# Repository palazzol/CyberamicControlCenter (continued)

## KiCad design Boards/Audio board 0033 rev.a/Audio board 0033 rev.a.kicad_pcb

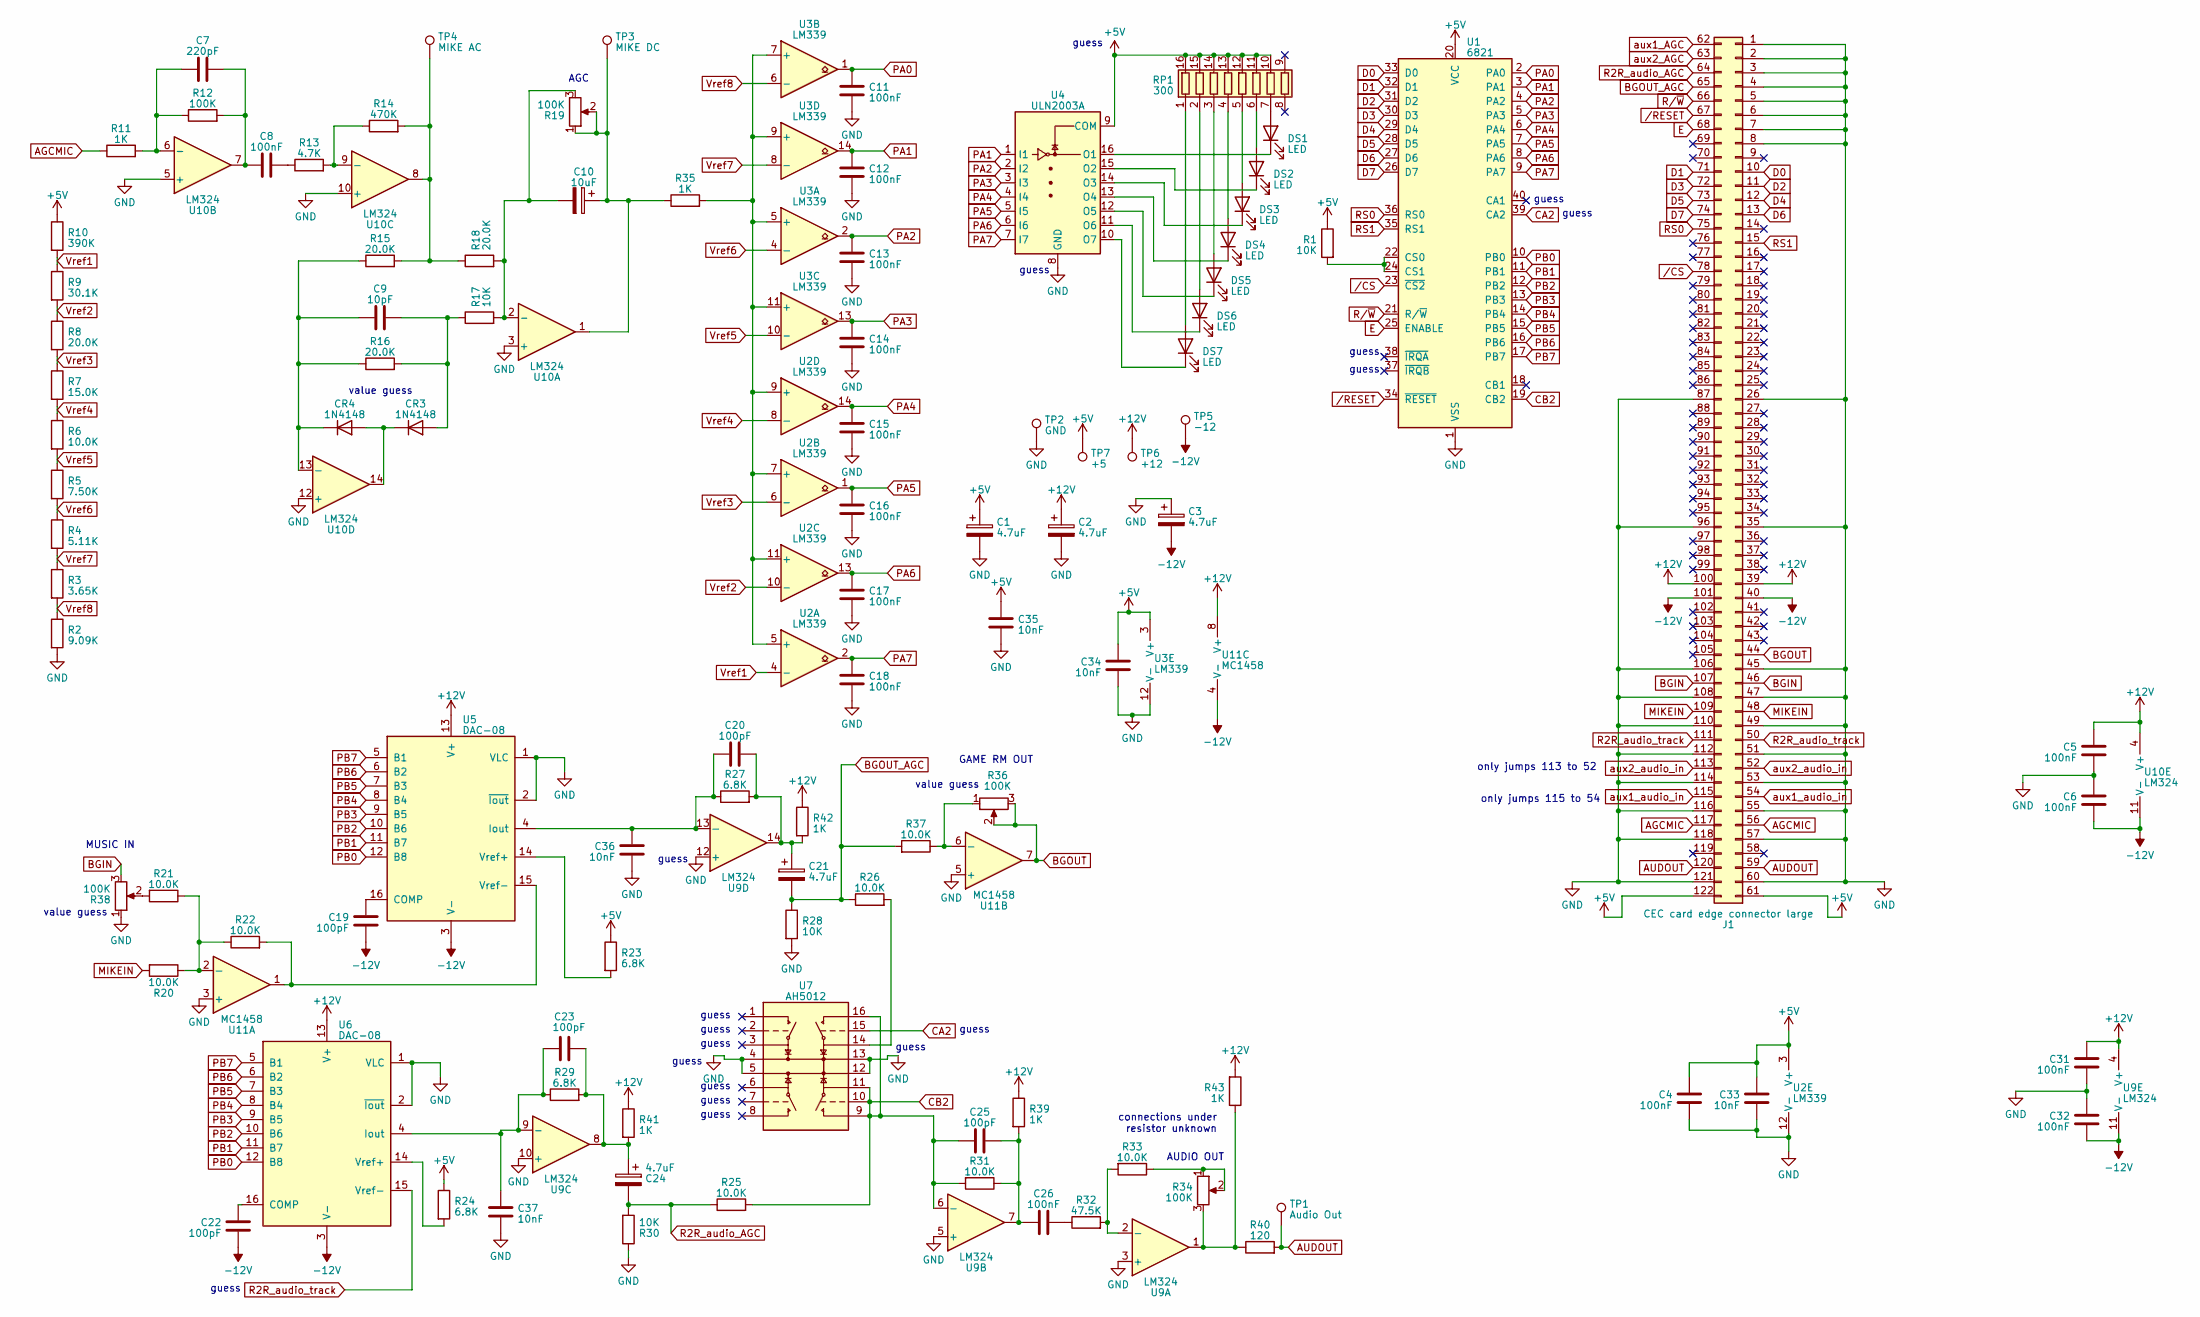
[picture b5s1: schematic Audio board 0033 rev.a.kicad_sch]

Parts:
C1, C2, C3, C21, C24: 4.7uF; CP_Radial_Tantal_D4mm_P3.81mm
C4, C5, C6, C8, C11, C12, C13, C14, C15, C16, C17, C18, C26, C31, C32: 100nF; C_Disc_D3.0mm_W1.6mm_P2.50mm
C7: 220pF; C_Rect_L7.0mm_W2.5mm_P5.00mm
C9: 10pF; C_Rect_L7.0mm_W2.5mm_P5.00mm
C10: 10uF; CP_Axial_L10.0mm_D4.5mm_P27.94mm_Horizontal
C19, C20, C22, C23, C25: 100pF; C_Rect_L7.0mm_W2.5mm_P5.00mm
C33, C34, C35: 10nF; C_Rect_L9.0mm_W2.5mm_P7.50mm_MKT
C36, C37: 10nF; C_Disc_D3.0mm_W1.6mm_P2.50mm
CR3, CR4: 1N4148; D_DO-35_SOD27_P7.62mm_Horizontal
DS1, DS2, DS3, DS4, DS5, DS6, DS7: LED; LED_D5.0mm_Horizontal_O3.81mm_Z15.0mm
J1: CEC card edge connector large; Chuck_E_Cheese_large_card_edge
R1, R17, R28, R30: 10K; R_Axial_DIN0309_L9.0mm_D3.2mm_P12.70mm_Horizontal
R2: 9.09K; R_Axial_DIN0309_L9.0mm_D3.2mm_P12.70mm_Horizontal
R3: 3.65K; R_Axial_DIN0309_L9.0mm_D3.2mm_P12.70mm_Horizontal
R4: 5.11K; R_Axial_DIN0309_L9.0mm_D3.2mm_P12.70mm_Horizontal
R5: 7.50K; R_Axial_DIN0309_L9.0mm_D3.2mm_P12.70mm_Horizontal
R6, R20, R21, R22, R25, R26, R31, R33, R37: 10.0K; R_Axial_DIN0309_L9.0mm_D3.2mm_P12.70mm_Horizontal
R7: 15.0K; R_Axial_DIN0309_L9.0mm_D3.2mm_P12.70mm_Horizontal
R8, R15, R16, R18: 20.0K; R_Axial_DIN0309_L9.0mm_D3.2mm_P12.70mm_Horizontal
R9: 30.1K; R_Axial_DIN0309_L9.0mm_D3.2mm_P12.70mm_Horizontal
R10: 390K; R_Axial_DIN0309_L9.0mm_D3.2mm_P12.70mm_Horizontal
R11, R35, R39, R41, R42, R43: 1K; R_Axial_DIN0309_L9.0mm_D3.2mm_P12.70mm_Horizontal
R12: 100K; R_Axial_DIN0309_L9.0mm_D3.2mm_P12.70mm_Horizontal
R13: 4.7K; R_Axial_DIN0309_L9.0mm_D3.2mm_P12.70mm_Horizontal
R14: 470K; R_Axial_DIN0309_L9.0mm_D3.2mm_P12.70mm_Horizontal
R19, R34, R36, R38: 100K; Potentiometer_Bourns_3005_Horizontal
R23, R24, R27, R29: 6.8K; R_Axial_DIN0309_L9.0mm_D3.2mm_P12.70mm_Horizontal
R32: 47.5K; R_Axial_DIN0309_L9.0mm_D3.2mm_P12.70mm_Horizontal
R40: 120; R_Axial_DIN0309_L9.0mm_D3.2mm_P12.70mm_Horizontal
RP1: 300; DIP-16_W7.62mm
TP1: Audio Out; TestPoint_Plated_Hole_D3.0mm
TP2: GND; TestPoint_Plated_Hole_D3.0mm
TP3: MIKE DC; TestPoint_Plated_Hole_D3.0mm
TP4: MIKE AC; TestPoint_Plated_Hole_D3.0mm
TP5: -12; TestPoint_Plated_Hole_D3.0mm
TP6: +12; TestPoint_Plated_Hole_D3.0mm
TP7: +5; TestPoint_Plated_Hole_D3.0mm
U1: 6821; DIP-40_W15.24mm
U2, U3: LM339; DIP-14_W7.62mm
U4: ULN2003A; DIP-16_W7.62mm
U5, U6: DAC-08; DIP-16_W7.62mm
U7: AH5012; DIP-16_W7.62mm
U9, U10: LM324; DIP-14_W7.62mm
U11: MC1458; DIP-8_W7.62mm

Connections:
+5V: C1.1, C4.1, C33.1, C34.1, C35.1, J1.61, J1.122, R1.1, R10.1, R23.1, R24.1, RP1.10 (R7.2), RP1.11 (R6.2), RP1.12 (R5.2), RP1.13 (R4.2), RP1.14 (R3.2), RP1.15 (R2.2), RP1.16 (R1.2), TP7.1, U1.20 (VCC), U2.3 (V+), U3.3 (V+), U4.9 (COM)
+12V: C2.1, C5.1, C31.2, J1.39, J1.100, R39.1, R41.1, R42.1, R43.2, TP6.1, U5.13 (V+), U6.13 (V+), U9.4 (V+), U10.4 (V+), U11.8 (V+)
-12V: C3.2, C6.2, C19.2, C22.2, C32.1, J1.40, J1.101, TP5.1, U5.3 (V-), U6.3 (V-), U9.11 (V-), U10.11 (V-), U11.4 (V-)
AGCMIC: J1.56, J1.117, R11.1
AUDOUT: J1.59, J1.120, R40.2, TP1.1
BGIN: J1.46, J1.107, R38.3
BGOUT: J1.44, R36.2, R36.3, U11.7
CA2: U1.39 (CA2), U7.15
D0: J1.10, U1.33 (D0)
D1: J1.71, U1.32 (D1)
D2: J1.11, U1.31 (D2)
D3: J1.72, U1.30 (D3)
D4: J1.12, U1.29 (D4)
D5: J1.73, U1.28 (D5)
D6: J1.13, U1.27 (D6)
D7: J1.74, U1.26 (D7)
E: J1.68, U1.25 (ENABLE)
GND: C1.2, C2.2, C3.1, C4.2, C5.2, C6.1, C11.2, C12.2, C13.2, C14.2, C15.2, C16.2, C17.2, C18.2, C31.1, C32.2, C33.2, C34.2, C35.2, C36.1, C37.1, J1.1, J1.2, J1.3, J1.4, J1.5, J1.6, J1.7, J1.8, J1.26, J1.35, J1.45, J1.47, J1.49, J1.51, J1.53, J1.55, J1.57, J1.60, J1.87, J1.96, J1.106, J1.108, J1.110, J1.112, J1.114, J1.116, J1.118, J1.121, R2.2, R28.2, R30.1, R38.1, TP2.1, U1.1 (VSS), U2.12 (V-), U3.12 (V-), U4.8 (GND), U5.1 (VLC), U5.2 (~Iout), U6.1 (VLC), U6.2 (~Iout), U7.4, U7.5, U7.12, U7.13, U9.3 (+), U9.5 (+), U9.10 (+), U9.12 (+), U10.3 (+), U10.5 (+), U10.10 (+), U10.12 (+), U11.3 (+), U11.5 (+)
MIKEIN: J1.48, J1.109, R20.2
unnamed: C7.2, C8.1, R12.2, U10.7
unnamed: C8.2, R13.1
unnamed: C10.1, R19.1, R19.2, R35.1, TP3.1, U10.1
unnamed: C20.2, C21.1, R27.2, R42.2, U9.14
unnamed: C23.2, C24.1, R29.2, R41.2, U9.8
unnamed: C25.1, C26.1, R31.1, R39.2, U9.7
unnamed: C26.2, R32.1
unnamed: C9.2, CR3.2 (A), R16.2, R17.1
unnamed: CR3.1 (K), CR4.2 (A), U10.14
unnamed: C9.1, CR4.1 (K), R15.1, R16.1, U10.13 (-)
unnamed: DS1.2 (A), RP1.7 (R7.1)
unnamed: DS1.1 (K), U4.16 (O1)
unnamed: DS2.2 (A), RP1.6 (R6.1)
unnamed: DS2.1 (K), U4.15 (O2)
unnamed: DS3.2 (A), RP1.5 (R5.1)
unnamed: DS3.1 (K), U4.14 (O3)
unnamed: DS4.2 (A), RP1.4 (R4.1)
unnamed: DS4.1 (K), U4.13 (O4)
unnamed: DS5.2 (A), RP1.3 (R3.1)
unnamed: DS5.1 (K), U4.12 (O5)
unnamed: DS6.2 (A), RP1.2 (R2.1)
unnamed: DS6.1 (K), U4.11 (O6)
unnamed: DS7.2 (A), RP1.1 (R1.1)
unnamed: DS7.1 (K), U4.10 (O7)
unnamed: R14.2, R15.2, R18.1, TP4.1, U10.8
unnamed: R21.2, R38.2
unnamed: R26.2, U7.14
unnamed: R33.1, R34.1, R34.2
unnamed: R34.3, R40.1, R43.1, U9.1
unnamed: R1.2, U1.22 (CS0), U1.24 (CS1)
unnamed: R35.2, U2.5 (+), U2.7 (+), U2.9 (+), U2.11 (+), U3.5 (+), U3.7 (+), U3.9 (+), U3.11 (+)
unnamed: C19.1, U5.16 (COMP)
unnamed: C20.1, C36.2, R27.1, U5.4 (Iout), U9.13 (-)
unnamed: R23.2, U5.14 (Vref+)
unnamed: R22.2, U5.15 (Vref-), U11.1
unnamed: C22.1, U6.16 (COMP)
unnamed: C23.1, C37.2, R29.1, U6.4 (Iout), U9.9 (-)
unnamed: R24.2, U6.14 (Vref+)
unnamed: R32.2, R33.2, U9.2 (-)
unnamed: C10.2, R17.2, R18.2, R19.3, U10.2 (-)
unnamed: C7.1, R11.2, R12.1, U10.6 (-)
unnamed: R13.2, R14.1, U10.9 (-)
unnamed: R20.1, R21.1, R22.1, U11.2 (-)
unnamed: R36.1, R37.1, U11.6 (-)
PA0: C11.1, U1.2 (PA0), U3.1
PA1: C12.1, U1.3 (PA1), U3.14, U4.1 (I1)
PA2: C13.1, U1.4 (PA2), U3.2, U4.2 (I2)
PA3: C14.1, U1.5 (PA3), U3.13, U4.3 (I3)
PA4: C15.1, U1.6 (PA4), U2.14, U4.4 (I4)
PA5: C16.1, U1.7 (PA5), U2.1, U4.5 (I5)
PA6: C17.1, U1.8 (PA6), U2.13, U4.6 (I6)
PA7: C18.1, U1.9 (PA7), U2.2, U4.7 (I7)
PB0: U1.10 (PB0), U5.12 (B8), U6.12 (B8)
PB1: U1.11 (PB1), U5.11 (B7), U6.11 (B7)
PB2: U1.12 (PB2), U5.10 (B6), U6.10 (B6)
PB3: U1.13 (PB3), U5.9 (B5), U6.9 (B5)
PB4: U1.14 (PB4), U5.8 (B4), U6.8 (B4)
PB5: U1.15 (PB5), U5.7 (B3), U6.7 (B3)
PB6: U1.16 (PB6), U5.6 (B2), U6.6 (B2)
PB7: U1.17 (PB7), U5.5 (B1), U6.5 (B1)
Pin 64: C24.2, J1.64, R25.1, R30.2
Pin 65: C21.2, J1.65, R26.1, R28.1, R37.2
Pin 113: J1.52, J1.113
Pin 115: J1.54, J1.115
R2R_audio_track: J1.50, J1.111, U6.15 (Vref-)
RS0: J1.75, U1.36 (RS0)
RS1: J1.15, U1.35 (RS1)
R/~W: J1.66, U1.21 (R/~W)
Vref1: R9.1, R10.2, U2.4 (-)
Vref2: R8.1, R9.2, U2.10 (-)
Vref3: R7.1, R8.2, U2.6 (-)
Vref4: R6.1, R7.2, U2.8 (-)
Vref5: R5.1, R6.2, U3.10 (-)
Vref6: R4.1, R5.2, U3.4 (-)
Vref7: R3.1, R4.2, U3.8 (-)
Vref8: R2.1, R3.2, U3.6 (-)
/CS: J1.78, U1.23 (~CS2)
/RESET: J1.67, U1.34 (~RESET)

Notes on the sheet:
guess
value guess
AGC
AUDIO OUT
GAME RM OUT
only jumps 115 to 54
connections under resistor unknown
only jumps 113 to 52
MUSIC IN

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
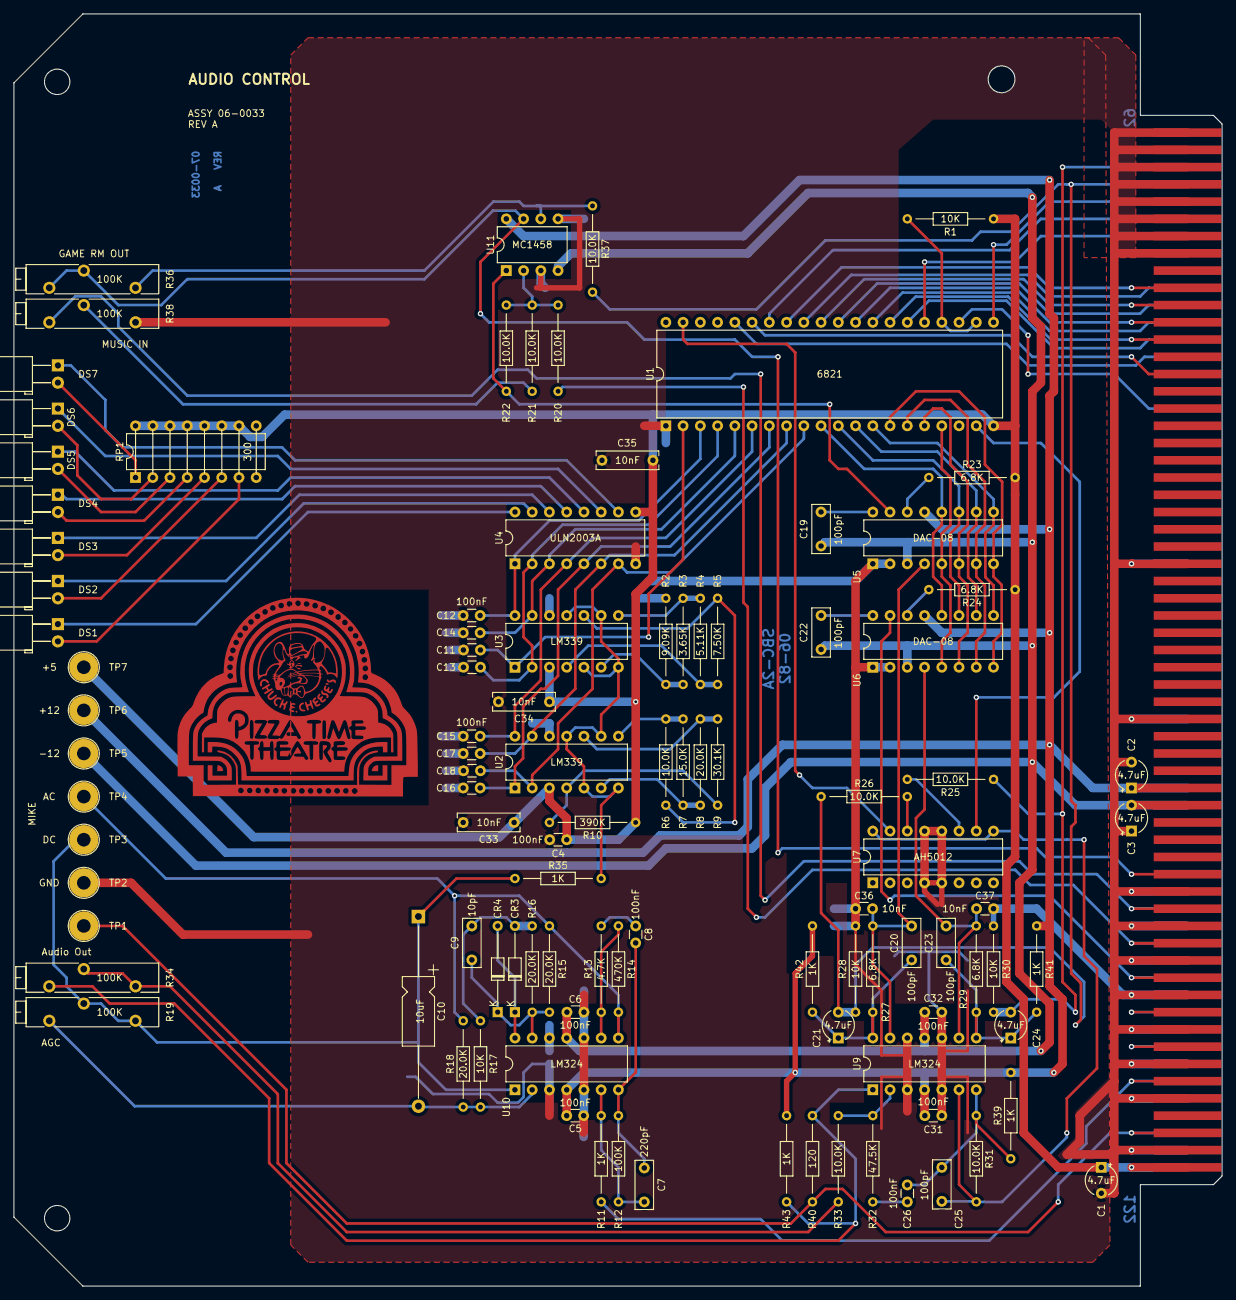
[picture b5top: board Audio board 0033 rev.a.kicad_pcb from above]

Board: 2 copper layers, 177.9 x 187.4 mm, 104 parts (0 on the bottom side), 100 nets.

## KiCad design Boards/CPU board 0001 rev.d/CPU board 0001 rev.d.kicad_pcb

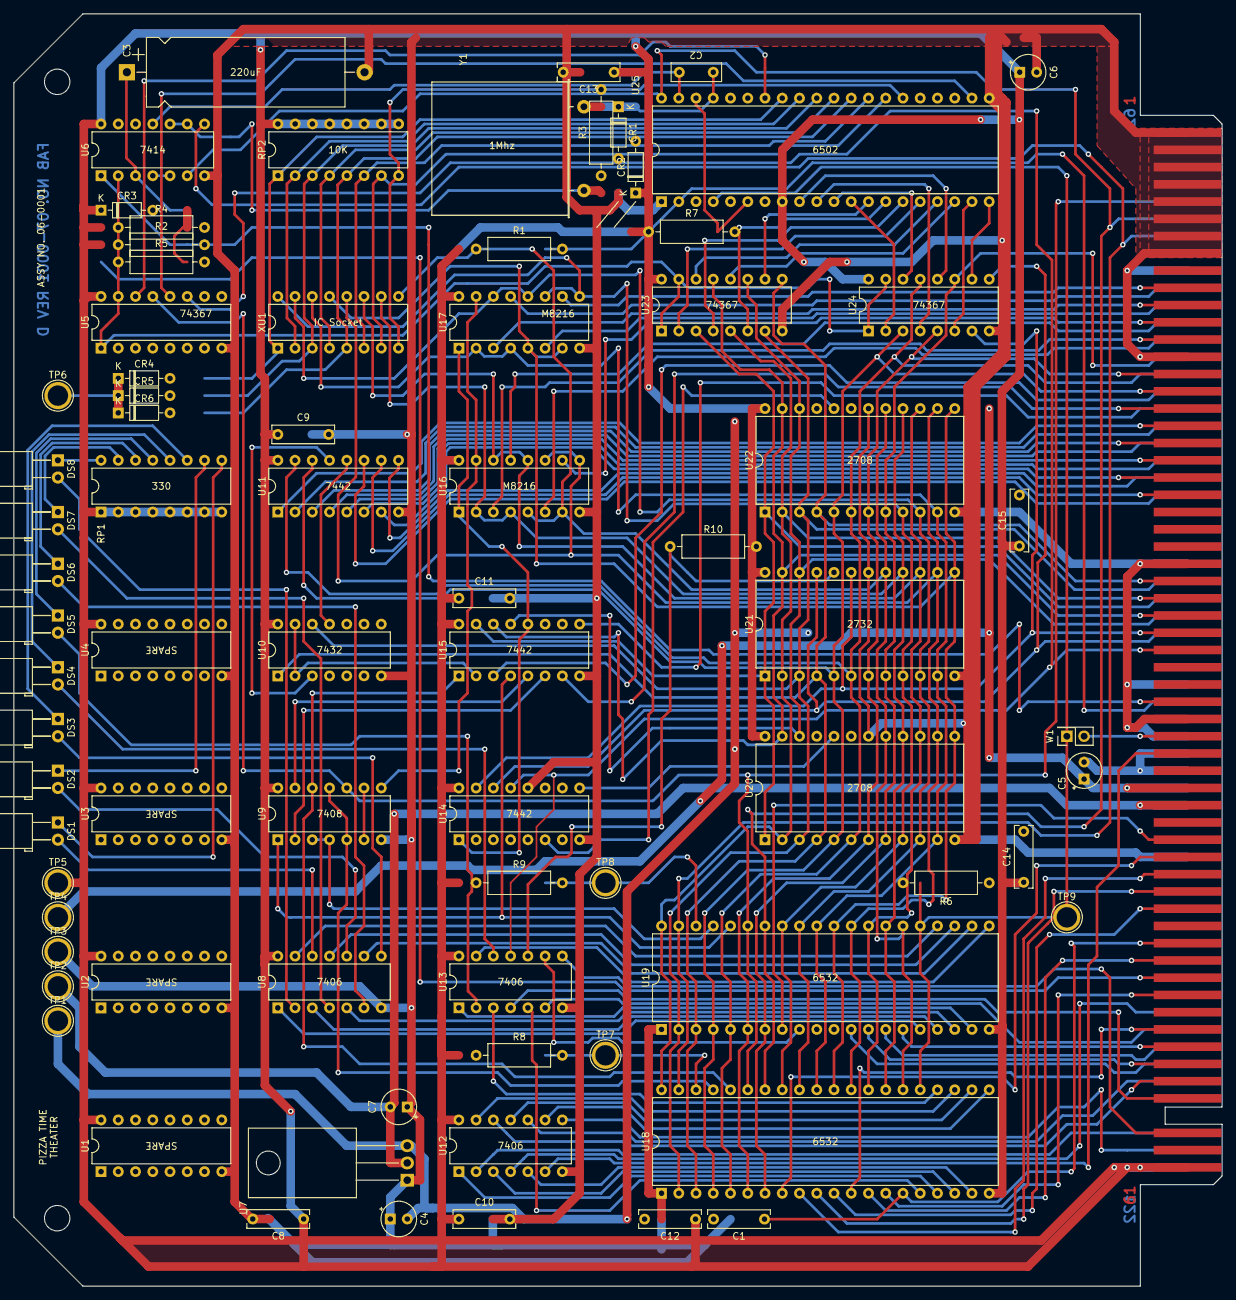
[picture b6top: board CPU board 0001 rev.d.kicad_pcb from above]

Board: 2 copper layers, 177.9 x 187.4 mm, 79 parts (0 on the bottom side), 157 nets.

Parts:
C1, C8, C9, C10, C11, C12, C13, C14, C15: 100nF; C_Rect_L9.0mm_W2.5mm_P7.50mm_MKT
C2: 10pF; C_Rect_L7.2mm_W2.5mm_P5.00mm_FKS2_FKP2_MKS2_MKP2
C3: 220uF; CP_Axial_L29.0mm_D10.0mm_P35.00mm_Horizontal
C4, C5, C6, C7: 4.7uF; CP_Radial_Tantal_D5.0mm_P2.50mm
CR1, CR2, CR3, CR4, CR5, CR6: 1N914; D_DO-35_SOD27_P7.62mm_Horizontal
DS1, DS2, DS3, DS4, DS5, DS6, DS7, DS8: LED; LED_D5.0mm_Horizontal_O3.81mm_Z15.0mm
J1: CEC card edge connector large; Chuck_E_Cheese_large_card_edge
R1, R2, R4, R6, R7, R8, R9: 4.7K; R_Axial_DIN0309_L9.0mm_D3.2mm_P12.70mm_Horizontal
R3: 330K; R_Axial_DIN0309_L9.0mm_D3.2mm_P12.70mm_Horizontal
R5: 100; R_Axial_DIN0309_L9.0mm_D3.2mm_P12.70mm_Horizontal
R10: 1K; R_Axial_DIN0309_L9.0mm_D3.2mm_P12.70mm_Horizontal
RP1: 330; DIP-16_W7.62mm
RP2: 10K; DIP-16_W7.62mm
TP1: -5v; TestPoint_Plated_Hole_D3.0mm
TP2: -12v; TestPoint_Plated_Hole_D3.0mm
TP3: GND; TestPoint_Plated_Hole_D3.0mm
TP4: +12v; TestPoint_Plated_Hole_D3.0mm
TP5: +5v; TestPoint_Plated_Hole_D3.0mm
TP6: ~{0/2/4}; TestPoint_Plated_Hole_D3.0mm
TP7: U18 CS; TestPoint_Plated_Hole_D3.0mm
TP8: U19 CS; TestPoint_Plated_Hole_D3.0mm
TP9: IRQ; TestPoint_Plated_Hole_D3.0mm
U1, U2, U3, U4: SPARE; DIP-16_W7.62mm
U5, U23, U24: 74367; DIP-16_W7.62mm
U6: 7414; DIP-14_W7.62mm
U7: LM7905_TO220; TO-220-3_Horizontal_TabDown
U8, U12, U13: 7406; DIP-14_W7.62mm
U9: 7408; DIP-14_W7.62mm
U10: 7432; DIP-14_W7.62mm
U11, U14, U15: 7442; DIP-16_W7.62mm
U16, U17: M8216; DIP-16_W7.62mm
U18, U19: 6532; DIP-40_W15.24mm
U20, U22: 2708; DIP-24_W15.24mm
U21: 2732; DIP-24_W15.24mm
U25: 6502; DIP-40_W15.24mm
W1: IRQ; PinSocket_2x01_P2.54mm_Vertical
XU1: IC Socket; DIP-16_W7.62mm
Y1: 1Mhz; Crystal_HC33-U_Horizontal

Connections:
+5V: C6.1, C8.1, C9.1, C10.1, C11.1, C12.1, C13.1, C14.1, C15.1, CR2.1 (K), CR3.1 (K), J1.61, J1.122, R1.1, R2.1, R4.1, R6.1, R7.1, R8.1, R9.1, R10.1, RP1.1 (R1.1), RP1.2 (R2.1), RP1.3 (R3.1), RP1.4 (R4.1), RP1.5 (R5.1), RP1.6 (R6.1), RP1.7 (R7.1), RP1.8 (R8.1), RP2.9 (R8.2), RP2.10 (R7.2), RP2.11 (R6.2), RP2.12 (R5.2), RP2.13 (R4.2), RP2.14 (R3.2), RP2.15 (R2.2), RP2.16 (R1.2), TP5.1, U1.16 (R1.2), U2.16 (R1.2), U3.16 (R1.2), U4.16 (R1.2), U5.16 (VCC), U6.14 (VCC), U8.14 (VCC), U9.14 (VCC), U10.14 (VCC), U11.16 (VCC), U12.14 (VCC), U13.14 (VCC), U14.16 (VCC), U15.16 (VCC), U16.16 (VCC), U17.16 (VCC), U18.20 (Vcc), U19.20 (Vcc), U20.24 (VCC), U21.24 (VCC), U22.24 (VCC), U23.16 (VCC), U24.16 (VCC), U25.8 (Vcc)
+12V: C5.1, J1.39, J1.100, TP4.1
-5V: C4.2, TP1.1, U7.3 (VO)
-12V: C7.2, J1.40, J1.101, TP2.1, U7.2 (VI)
A0: U24.12 (I5), U25.9 (A0)
A1: U24.4 (I2), U25.10 (A1)
A2: U24.14 (I6), U25.11 (A2)
A3: U24.2 (I1), U25.12 (A3)
A4: U23.10 (I4), U25.13 (A4)
A5: U23.6 (I3), U25.14 (A5)
A6: U23.4 (I2), U25.15 (A6)
A7: U23.2 (I1), U25.16 (A7)
A8: U23.14 (I6), U25.17 (A8)
A9: U23.12 (I5), U25.18 (A9)
A10: U24.6 (I3), U25.19 (A10)
A11: U24.10 (I4), U25.20 (A11)
A12: U5.12 (I5), U25.22 (A12)
AGC 1: J1.116, U19.12 (PA4)
AGC 2: J1.55, U19.13 (PA5)
AGC 4: J1.115, U19.14 (PA6)
AGC 8: J1.54, U19.15 (PA7)
AUDIO: J1.78, U15.9 (7)
B'DAY in: J1.44, U18.9 (PA1)
B'DAY out: J1.56, U12.12
BA0: J1.75, U18.7 (A0), U19.7 (A0), U20.8 (A0), U21.8 (A0), U22.8 (A0), U24.11 (O5b)
BA1: J1.15, U18.6 (A1), U19.6 (A1), U20.7 (A1), U21.7 (A1), U22.7 (A1), U24.5 (O2a)
BA2: J1.76, U11.15 (A0), U18.5 (A2), U19.5 (A2), U20.6 (A2), U21.6 (A2), U22.6 (A2), U24.13 (O6b)
BA3: J1.16, U11.14 (A1), U18.4 (A3), U19.4 (A3), U20.5 (A3), U21.5 (A3), U22.5 (A3), U24.3 (O1a)
BA4: J1.27, U10.1, U18.3 (A4), U19.3 (A4), U20.4 (A4), U21.4 (A4), U22.4 (A4), U23.9 (O4a)
BA5: J1.88, U10.12, U18.2 (A5), U19.2 (A5), U20.3 (A5), U21.3 (A5), U22.3 (A5), U23.7 (O3a)
BA6: J1.28, U18.40 (A6), U19.40 (A6), U20.2 (A6), U21.2 (A6), U22.2 (A6), U23.5 (O2a)
BA7: J1.89, U15.15 (A0), U20.1 (A7), U21.1 (A7), U22.1 (A7), U23.3 (O1a)
BA8: J1.29, U15.14 (A1), U20.23 (A8), U21.23 (A8), U22.23 (A8), U23.13 (O6b)
BA9: J1.90, U15.13 (A2), U20.22 (A9), U21.22 (A9), U22.22 (A9), U23.11 (O5b)
BA10: J1.30, U14.15 (A0), U21.19 (A10), U24.7 (O3a)
BA11: J1.91, U14.14 (A1), U21.21 (A11), U24.9 (O4a)
BA12: J1.31, U5.11 (O5b), U13.11, U14.13 (A2)
BS1: J1.18, U11.1 (0)
BS2: J1.79, U11.2 (1)
BS3: J1.19, U11.3 (2)
BS4: J1.80, U11.4 (3)
BS5: J1.20, U11.5 (4)
BS6: J1.81, U11.6 (5)
BS7: J1.21, U11.7 (6)
BS8: J1.82, U11.9 (7)
BS9: J1.22, U11.10 (8)
BS10: J1.83, U11.11 (9)
CHEER in: J1.43, U18.8 (PA0)
CHEER out: J1.57, U13.4
D0: U17.9 (DI2), U17.11 (DO2), U18.33 (D0), U19.33 (D0), U20.9 (D0), U21.9 (D0), U22.9 (D0), XU1.16 (R1.2)
D1: U17.12 (DI3), U17.14 (DO3), U18.32 (D1), U19.32 (D1), U20.10 (D1), U21.10 (D1), U22.10 (D1), XU1.15 (R2.2)
D2: U17.2 (DO0), U17.4 (DI0), U18.31 (D2), U19.31 (D2), U20.11 (D2), U21.11 (D2), U22.11 (D2), XU1.14 (R3.2)
D3: U17.5 (DO1), U17.7 (DI1), U18.30 (D3), U19.30 (D3), U20.13 (D3), U21.13 (D3), U22.13 (D3), XU1.13 (R4.2)
D4: U16.9 (DI2), U16.11 (DO2), U18.29 (D4), U19.29 (D4), U20.14 (D4), U21.14 (D4), U22.14 (D4), XU1.12 (R5.2)
D5: U16.12 (DI3), U16.14 (DO3), U18.28 (D5), U19.28 (D5), U20.15 (D5), U21.15 (D5), U22.15 (D5), XU1.11 (R6.2)
D6: U16.2 (DO0), U16.4 (DI0), U18.27 (D6), U19.27 (D6), U20.16 (D6), U21.16 (D6), U22.16 (D6), XU1.10 (R7.2)
D7: U16.5 (DO1), U16.7 (DI1), U18.26 (D7), U19.26 (D7), U20.17 (D7), U21.17 (D7), U22.17 (D7), XU1.9 (R8.2)
DB0: J1.10, U17.10 (DB2)
DB1: J1.71, U17.13 (DB3)
DB2: J1.11, U17.3 (DB0)
DB3: J1.72, U17.6 (DB1)
DB4: J1.12, U16.10 (DB2)
DB5: J1.73, U16.13 (DB3)
DB6: J1.13, U16.3 (DB0)
DB7: J1.74, U16.6 (DB1)
DIAG in: J1.53, U18.12 (PA4)
DIAG out: J1.37, U12.6
GND: C1.2, C3.2, C4.1, C5.2, C6.2, C7.1, C8.2, C9.2, C10.2, C11.2, C12.2, C13.2, C14.2, C15.2, CR1.2 (A), J1.1, J1.2, J1.3, J1.4, J1.5, J1.6, J1.7, J1.8, J1.14, J1.26, J1.35, J1.70, J1.87, J1.94, J1.97, J1.98, J1.99, J1.103, J1.104, J1.105, J1.106, J1.107, J1.108, J1.109, J1.110, J1.111, J1.112, TP3.1, U1.8 (R8.1), U2.8 (R8.1), U3.8 (R8.1), U4.8 (R8.1), U5.8 (GND), U6.7 (GND), U7.1 (GND), U8.7 (GND), U9.7 (GND), U10.7 (GND), U11.8 (GND), U12.7 (GND), U13.7 (GND), U14.8 (GND), U14.12 (A3), U15.8 (GND), U16.8 (GND), U17.8 (GND), U18.1 (GND), U19.1 (GND), U20.12 (GND), U20.18 (PGM), U21.12 (GND), U21.18 (~CE), U22.12 (GND), U22.18 (PGM), U23.8 (GND), U24.8 (GND), U25.1 (VSS), U25.21 (GND)
INTRO in: J1.45, U18.10 (PA2)
INTRO out: J1.117, U12.10
MIKE SW.: J1.42, U19.8 (PA0)
NEXT in: J1.49, U18.13 (PA5)
NEXT out: J1.113, U12.4
unnamed: C2.1, CR1.1 (K), CR2.2 (A), R3.2, U25.37 (00), Y1.1
unnamed: C3.1, CR3.2 (A), R4.2, R5.2, U6.3
unnamed: CR4.2 (A), RP2.1 (R1.1), U25.33 (D0), XU1.1 (R1.1)
unnamed: CR4.1 (K), CR5.1 (K), CR6.1 (K), TP6.1
unnamed: CR5.2 (A), RP2.3 (R3.1), U25.31 (D2), XU1.3 (R3.1)
unnamed: CR6.2 (A), RP2.5 (R5.1), U25.29 (D4), XU1.5 (R5.1)
unnamed: DS1.2 (A), RP1.9 (R8.2)
unnamed: DS1.1 (K), U8.12
unnamed: DS2.2 (A), RP1.10 (R7.2)
unnamed: DS2.1 (K), U8.10
unnamed: DS3.2 (A), RP1.11 (R6.2)
unnamed: DS3.1 (K), U8.8
unnamed: DS4.2 (A), RP1.12 (R5.2)
unnamed: DS4.1 (K), U13.12
unnamed: DS5.2 (A), RP1.13 (R4.2)
unnamed: DS5.1 (K), U13.2
unnamed: DS6.2 (A), RP1.14 (R3.2)
unnamed: DS6.1 (K), U8.6
unnamed: DS7.2 (A), RP1.15 (R2.2)
unnamed: DS7.1 (K), U8.4
unnamed: DS8.2 (A), RP1.16 (R1.2)
unnamed: DS8.1 (K), U8.2
unnamed: R3.1, U6.9, U6.10, Y1.2
unnamed: RP2.2 (R2.1), U25.32 (D1), XU1.2 (R2.1)
unnamed: RP2.4 (R4.1), U25.30 (D3), XU1.4 (R4.1)
unnamed: RP2.6 (R6.1), U25.28 (D5), XU1.6 (R6.1)
unnamed: RP2.7 (R7.1), U25.27 (D6), XU1.7 (R7.1)
unnamed: RP2.8 (R8.1), U25.26 (D7), XU1.8 (R8.1)
unnamed: U6.4, U6.5
unnamed: U9.6, U9.9
unnamed: U10.3, U11.13 (A2)
unnamed: U10.11, U11.12 (A3)
unnamed: U14.1 (0), U15.12 (A3), U16.1 (~CS), U17.1 (~CS)
unnamed: U9.8, U16.15 (IN/~OUT), U17.15 (IN/~OUT)
unnamed: R8.2, TP7.1, U18.38 (CS1)
unnamed: U13.3, U18.24 (PB0)
unnamed: U12.13, U18.23 (PB1)
unnamed: U12.11, U18.22 (PB2)
unnamed: U12.9, U18.21 (PB3)
unnamed: U12.5, U18.19 (PB4)
unnamed: U12.3, U18.18 (PB5)
unnamed: U12.1, U18.17 (PB6)
unnamed: U13.5, U18.16 (PB7)
unnamed: U9.5, U9.11, U18.37 (~CS2)
unnamed: R9.2, TP8.1, U19.38 (CS1)
unnamed: U13.9, U19.9 (PA1)
unnamed: U8.13, U19.24 (PB0)
unnamed: U8.11, U19.23 (PB1)
unnamed: U8.9, U19.22 (PB2)
unnamed: U13.13, U19.21 (PB3)
unnamed: U13.1, U19.19 (PB4)
unnamed: U8.5, U19.18 (PB5)
unnamed: U8.3, U19.17 (PB6)
unnamed: U8.1, U19.16 (PB7)
unnamed: U9.3, U9.4, U19.37 (~CS2)
unnamed: U5.1 (OEa), U5.15 (OEb), U6.2, U23.1 (OEa), U23.15 (OEb), U24.1 (OEa), U24.15 (OEb)
unnamed: C2.2, U6.11, U25.39 (02)
unnamed: R7.2, U25.6 (~NMI), U25.38 (SO)
PHI2: J1.68, U6.8, U18.39 (02), U19.39 (02)
PROG in: C1.1, J1.48, U18.15 (PA7)
PROG out: J1.114, U13.6
RDY: J1.95, R1.2, U25.2 (RDY)
RESET out: J1.59, U13.8
R/~W: J1.66, U5.13 (O6b), U9.10, U18.35 (R/~W), U19.35 (R/~W)
SKIP in: J1.51, U18.14 (PA6)
SKIP out: J1.120, U12.2
SPEC in: J1.46, U18.11 (PA3)
SPEC out: J1.121, U12.8
UART: J1.77, U15.3 (2)
XPRT: J1.17, U15.7 (6)
cpu R/~W: U5.14 (I6), U25.34 (R/~W)
/CARDS: U10.2, U10.13, U15.2 (1)
/CS 2732: R10.2, U13.10, U21.20 (~OE/VPP)
/CS U20: U14.9 (7), U20.20 (~CS)
/CS U22: U14.6 (5), U22.20 (~CS)
/HOLD in: J1.34, R2.2, U6.1
/IRQ: R6.2, TP9.1, U18.25 (~IRQ), U19.25 (~IRQ), U25.4 (~IRQ), W1.1
/IRQ out: J1.36, W1.2
/RAM: U9.12, U15.1 (0), U18.36 (/RS)
/RESET: J1.67, U6.6, U18.34 (~RESET), U19.34 (~RESET), U25.40 (~RESET)
/RESET in: J1.50, R5.1
/STACK: U9.1, U15.4 (3), U19.36 (/RS)
/U18: U9.13, U15.5 (4)
/U19: U9.2, U15.6 (5)

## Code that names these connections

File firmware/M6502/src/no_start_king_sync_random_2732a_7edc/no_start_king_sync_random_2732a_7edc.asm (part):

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;
IRQ:
        pha
        lda     U18_edge_detect_control_DI_pos          ; clear PA7 flag
        lda     U19_edge_detect_control_DI_pos          ; clear PA7 flag
        lda     #0x7D                                   ; expire every 125*8=1000us=1ms
        sta     U18_1D                                  ; div by 8, enable interrupt
        lda     TIMER_1MS_A                             ; 1ms timer
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        sta     U18_DDRB                                ; Button lights are outputs
        sta     U19_DDRB                                ; CPU card lights are outputs
        lda     #0xFC
        sta     transport_periph$ddr_reg_b              ; transport control, chip control are outputs, PB1 & PB0 inputs
        lda     #0x2E
        sta     transport_control_reg_a                 ; transport CA2 is Read strobe (~DDR), set IRQA bit on ~DR low to high 
        sta     transport_control_reg_b                 ; transport CB2 is Write strobe (~THRL), set IRQB bit on CB1 low to high
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PLAYTRK:
        lda     transport_periph$ddr_reg_a
        lda     #0x40
        sta     board_1_periph$ddr_reg_b                ; only Board 1 PB6 on
        sta     board_2_periph$ddr_reg_b                ; only Board 2 PB6 on
        sta     board_3_periph$ddr_reg_b                ; only Board 3 PB6 on
        sta     board_4_periph$ddr_reg_b                ; only Board 4 PB6 on
        lda     #0x3C
        sta     audio_control_reg_a                     ; CA2 High (Disable Other Audio)
        lda     #0x34
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
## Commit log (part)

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2024-02-19 Add rudimentary FAQ file
2024-03-02 Add some notes on audio board
2024-03-03 started audio card rev a
2024-03-03 added pictures from San Jose trip
2024-03-04 Add 6502 bins and disassemblies
    Add link to HC11 disassembly
2024-03-04 added pictures of notes taken
2024-03-04 make board indices consistent
2024-03-05 Add TEAC X-7RMKII service manual
2024-03-06 audio board rev a agc circuit probably complete
2024-03-06 sorted out U11 and some of the card edge
2024-03-06 working on U9 section
2024-03-06 half of u9 done
2024-03-06 finished initial layout and added backplane notes from san jose trip
2024-03-06 fixed resistor value, moved bgaudio amp to logical location
2024-03-06 board outline done, picking footprints
2024-03-06 more footprints
2024-03-07 U7/U9 area laid out, best guess on 0.025" grid for silk, 0.05" grid for parts
2024-03-07 initial placement of components done
2024-03-08 most of layout done, fixed some bugs
2024-03-08 front copper fill done
2024-03-08 layout done minus logo
2024-03-09 tweaked backplane wording to reflect schematic date
2024-03-09 renamed file that will be used for copper layer logo
2024-03-09 initial rev c layout completed
2024-03-09 layout tweaks to reva
2024-03-09 silk tweaks reva
2024-03-09 silk tweaks revc
2024-03-09 tweaked copper fills on revc
2024-03-09 tweaked copper fills reva
2024-03-09 copper layer on reva
2024-03-09 updated some labels on backplane from audio cards
2024-03-09 labeled pins 64 and 65
2024-03-09 moved cpu schematic pictures to the right folder
2024-03-10 added pics from cheese e pedia
2024-03-11 Update board indicies
2024-03-11 minor jun
2024-03-15 More Disassembly Comments
2024-03-16 Add two pages
2024-03-16 Add some .gitignore files
2024-03-17 revised hole position in audio cards based on character card
2024-03-17 initial character card rev a parts and partial layout
2024-03-17 character card rev a done
2024-03-17 revised copper layer character card rev a
2024-03-17 revised schematic to more match paper one
2024-03-17 character card rev b done
2024-03-17 revised all net names to reflect new information about 4 channel audio system
2024-03-17 renaming a lot of files to be more explicit
2024-03-17 updated boards to have correct logos
2024-03-18 completed 0034 rev a
2024-03-18 revised LED spacing
2024-03-18 starting the first rev character driver compatible with the av switcher
2024-03-18 tweaking silk
2024-03-18 revised LED spacing rev a
2024-03-18 revised 0034 rev a led spacing and fuse length
2024-03-18 rev d layout done
2024-03-18 renamed files and started the light card
2024-03-19 added logos
2024-03-19 one chip misplaced
2024-03-19 almost done with the old light driver
2024-03-19 finish light board rev.a, rename files, add renders and schematics, move pictures
2024-03-19 finished 0021 rev f
2024-03-19 revised notes
2024-03-19 tweaks for transport board
2024-03-19 starting transport board schematic (1982)
2024-03-19 finished schematic (incorrect) digitization
2024-03-19 revised some test points per pictures of real boards
2024-03-20 added changelog
2024-03-20 working on transport card rev.b
2024-03-20 added ref des note
2024-03-20 transport card digital section almost done
2024-03-21 rev.b and rev.d transport cards done?
2024-03-21 typo
2024-03-21 started cpu board
2024-03-21 revised test point names
2024-03-21 half done routing cpu rev.a
2024-03-22 continued routing
2024-03-22 finished rev.a layout
2024-03-22 Small updates regarding start of tape detection
2024-03-22 Notes on required modifications to tape decks
2024-03-22 Add transport card notes
2024-03-23 Updated PCB generations doc
    Added questions doc
2024-03-23 Fix spelling errors with Transport
2024-03-23 Add TEAC X-7R / X-7 service manual
2024-03-23 Update readme.txt
    moved information from questions.txt
2024-03-23 removed questions.txt
2024-03-23 fixed tabs
2024-03-23 board 0002?
2024-03-24 added some notes for the cpu board
2024-03-24 added cpu notes doc
2024-03-26 checked Rev.c cpu board and tweaked copper on a and b
2024-03-26 finished rev.d according to paper schematic
2024-04-01 added solenoid board pics
2024-04-01 tweaks while writing blog entries
2024-04-03 removed question, I think I know
2024-04-04 tweaked for production
2024-04-18 Add "Dolli C" EPROM image
2024-04-18 Add readme files for half-a-chuck EPROMs
2024-04-18 Add Unknown2 EPROM image
2024-04-18 Add Unknown1 EPROM image
2024-04-18 Add Main Stage EPROM image, rebuildable from disassembled source
2024-04-18 Fix a readme
2024-04-18 Add full versions
2024-04-19 Switch halfchuck to rebuildable assembly
2024-04-19 Switch halfchuckorange to rebuildable assembly
2024-04-19 Corrected halfchuckorange reconstructed image
2024-04-19 Update unknown1 to be rebuildable
2024-04-19 Make dolli_c rebuildable
2024-04-19 Make unknown2 rebuildable
2024-04-19 Remove the last of the tabs
2024-04-19 Small tweaks
2024-04-23 updated boards per real one
2024-04-24 sent off boards for manufacture
2024-04-30 revisions from real life boards
    tip130a is actually tip30a, widened holes for crystal, widened holes for big power resistor, fixed cpu board LED resistors
2024-04-30 revised value of resistor to 1k per board
2024-05-03 added plans for 8216 substiturte board
2024-05-05 added old adapter from previous repo
2024-05-20 revised PCBs based on Jen's boards, added rev.c
2024-05-20 started solenoid board
2024-05-20 layout of solenoid board done
2024-05-20 added renders for solenoid board
2024-05-23 added button board initial schematic (no custom buttons yet)
2024-05-26 button board done
2024-05-26 Commonize peripheral addresses into ptt6502.def
2024-05-26 Fix typo
2024-05-26 Regularize RAM variables. Add missing def file.
2024-05-27 Some more small tweaks, better naming, comments
2024-05-28 Moved Cyberstar1.6 repo to here
2024-05-28 Add initial Cyberstar 1.7 image
2024-05-29 Cyberstar 1.7 Reassembles now. Small changes, and 2 new routines compared to Cyberstar 1.6
2024-05-29 Tweak Readme, remove old unidasm disassembly listing
2024-05-30 Disassembled new code from Cyberstar1.7 more correctly. Added new labels for all Branch addresses consistently
2024-05-30 Decode ascii commands and responses from monitor code
2024-05-31 Try to fix github rendering of .rst files
2024-06-15 Remove out of date images
2024-06-15 Update comments on curtains, baud rate, serial diagnostic stuff, some of MINI-MON
2024-07-07 Updated diassemblies. Removed old ramusage.txt
2024-07-09 Named routines, updated disassemblies
2024-07-09 More disassembly updates
2024-07-09 Add updated defines file
2024-07-09 Add Dolli disassembly comments
2024-07-11 More Updates to Dolli and Main Stage Disassemblies
2024-07-11 Add preliminary channel mappings doc
2024-07-28 fixed 50 pin ribbon, added 3d models
2024-08-19 50 pin adapter fab
2024-08-19 8216 adapter fab
2024-08-19 changed kicad version
2024-08-19 new solenoid board
2024-08-19 fixed rev.d pull up on CS and added render and schematic
2024-08-22 added lcd board
2024-08-30 added LCD mount adapter and new version of LCD board for modern LCDs
2025-02-22 Add TEAC cap info
2025-02-22 New pics
2025-02-22 Update Main Stage diasassembly
2025-02-22 Add redundant rebuilt bins because they are too hard to filter
2025-02-22 One more .gitignore update
2025-02-22 Cleanup old roms folder
2025-02-22 Add a couple misc files
2025-03-20 added new de9 boards
2025-04-18 added audio board schematics and de9 board fab files
2025-05-08 transport board silk update
2025-05-31 added images of blank boards from ebay
2025-08-24 New dumps
2025-11-06 added images with which to revise card designs (from Boris)
2026-01-13 added lights DE9 adapter
2026-01-26 fixed typo
2026-02-02 added roms for cyberstar 3.2 and 3.3
2026-02-11 changes from ordering lights de9 adapter
2026-02-14 Fix line endings
2026-02-14 Cleanup
2026-02-14 EPROM Updates
2026-03-11 Add tx_king disassembly. Switched to linux build script
2026-03-11 Add json used for initial disassembly
2026-03-11 Add 017-0001-10_flex_stage_8_min_f101 and disassembly
2026-03-11 Add 017-0028-01_stage_flex_rnd_6min_2732a_336b
2026-03-11 Add 017-0120-01_stg_3m_dif_live_sync_2732a_afd8 disassembly
2026-03-12 Added 017-0160-01_cec_cyberstar_all_4-13-92_1990_0572 disassembly
2026-03-12 Added 017-0160-01_kingbeagles_sync_799d disassembly
2026-03-12 Added king_sync_test-version_5-26-88_7ed5 disassembly
2026-03-12 Fix wrong build script
2026-03-12 Add no_start_king_sync_random_2732a_7edc disassembly
2026-03-12 Update 015-0020-10_REV_L_FREE_BEAGKING_1c00_5efe_u20
2026-03-12 Small tweak to tx_king.rst
2026-03-12 Updated dolli_c
2026-03-12 Updated stage_flex_sync_rnd_test_version_5-26-88_03bb
2026-03-12 Updated unknown1_beagking
2026-03-12 Updated halfchuck
2026-03-12 Updated halfchuck_orange
2026-03-12 Remove some redundant files
2026-03-12 Rearrange M6502 source directories
2026-03-12 Add a couple missing symbols
2026-03-12 Add explicit zero fill gaps where necessary
2026-03-12 Combine build scripts. Add buildall script
2026-03-12 Add missing build script!
2026-03-13 Added diassembly off partial set 015-0001-10_rev_m-4_stage_1800_u21_4min
2026-03-13 Added partial king disassembly
2026-03-13 Add partial disassemblies of no_label and no_label_3
2026-03-14 Fix issue with serial number
2026-05-16 Small doc update
2026-05-23 dollic: Name RAM variables
2026-05-23 Name some more labels
2026-05-23 Label RAM variables
2026-05-24 Name RAM Variables
2026-06-06 Update top level readme
